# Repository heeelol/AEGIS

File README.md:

# AEGIS: AI-Enhanced Guidance and Inspection System

AEGIS is a computer vision and sensor-assisted system designed to reduce errors in manual kitting, the process by which a worker selects and packs a specified set of components into a single kit. The project was developed as the final year capstone for the CDE3301/IS305 module at the National University of Singapore (AY2025/26), in partnership with TE Connectivity and with hardware sponsorship from Advantech.

*The complete AEGIS workstation: overhead camera mount, load-cell bin platforms, operator dashboard, and the AI PC that runs the detection pipeline.*

## The Problem

In high-mix, low-volume manufacturing environments, kitting is performed manually because the variety of parts makes full automation impractical. This reliance on manual work introduces the risk of wrong parts, missing parts, and incorrect quantities. According to TE Connectivity, these errors account for an estimated USD 10,000 to USD 20,000 in losses per production line each year, largely because defects are only discovered downstream, where they are far more costly and difficult to trace back to their source.

## Our Approach

Rather than inspecting a kit after it has been packed, AEGIS observes the packing process as it happens. An overhead camera tracks the operator's hand movements to determine which bin is being accessed, while load cells positioned beneath each bin measure the change in weight for every pick. Together, these two independent signals allow the system to confirm, in real time, whether the correct item and the correct quantity have been taken. When a discrepancy is detected, the operator is alerted immediately through a dashboard interface, before the kit moves further down the line.

This dual-sensor design was a deliberate choice. Rather than requiring the system to visually identify each individual component, which is difficult given how frequently TE Connectivity's parts catalogue changes, AEGIS instead recognizes bins and cross-references their known contents with the weight removed. This keeps the system maintainable by production staff without requiring specialist machine learning expertise for every new part introduced.

## System Overview

The workstation is organized into three layers that work together as a closed loop:

- **Physical layer.** An aluminum-extrusion gantry holds the camera overhead and supports a modular arrangement of load-cell bin platforms and kitting bins.
- **Sensor layer.** A camera tracks the operator's hands, while load cells beneath each bin register mass changes as items are picked.
- **Software layer.** An edge processing engine, running locally on an Advantech MIC-733-AO industrial AI PC (built on an NVIDIA Jetson AGX Orin), combines the two sensor streams and checks them against the kit's bill of materials. Results are pushed to a dashboard on an Advantech FPM-215 touchscreen, giving the operator immediate, visual feedback.

Running all processing locally, rather than in the cloud, was a requirement from TE Connectivity to keep production data on-site and to avoid any dependence on network latency.

## Demonstration

A stitched video recording of the system in operation, combining the camera's point of view, the operator dashboard, and a third-person view of an operator performing a kitting task, can be viewed on YouTube: <https://youtu.be/AxHCu2dXehM>.

## Results

The system was evaluated through both developer-led testing and structured user testing with operators.

- Component identification was shown to be reliable across a range of lighting conditions and bin fill levels, and the backend fault-detection logic passed 134 unit tests covering 98 percent of the core decision-making code.
- In user testing with six operators, AEGIS was rated highly for communicating what to pack and how much to pack, and was generally preferred over a paper-based instruction sheet.
- The same testing also found that AEGIS introduced a consistent cycle-time increase of 35.2 percent across all operators, which did not meet the project's original performance target and is noted as the most significant area for further development.
- In a closing evaluation session, a TE Connectivity stakeholder rated the prototype's readiness for deployment at 80 percent, attributing most of the remaining gap to configuration workflow rather than to detection accuracy or hardware reliability.
- A cost analysis found that the base configuration of the system remains within budget expectations and pays for itself well inside a typical evaluation period.

Taken together, these findings support AEGIS as a proof of concept: the underlying idea, that errors can be caught at the moment they occur rather than after the fact, is validated, while its operating speed and ease of configuration remain the primary items to address before the system would be ready for a live production floor.

## Repository Structure

| Folder | Description |
| --- | --- |
| `final report/` | The final written report submitted for assessment, the demonstration video, supporting source material, and setup photography. |
| `aegis-v2/` | The current version of the bin-tracking and hand-tracking pipeline that powers the live system, along with its computer vision models and integration code. |
| `aegis-cv/` | Earlier computer vision model training and evaluation work. |
| `kitting-error-tracker/` | A standalone tool for tracking kitting errors during testing. |
| `esp32/` | Firmware and PCB design files for the load-cell electronics. |
| `Complete model/` | An earlier consolidated version of the detection and tracking pipeline. |

## Project Team

Developed by Lim Kai Ler Ethan, Aw Shuo Jie, Yap Jia Wei, and Yeo Chen Xian, under the supervision of Mr Chan Tong Leong and Mr Eugene Ee, as part of NUS's Engineering Design and Innovation Centre programme.

## Acknowledgements

We are grateful to TE Connectivity for the problem context and their continued involvement in testing and evaluating the prototype, and to Advantech for sponsoring the MIC-733-AO AI PC and FPM-215 HMI used throughout development. Full acknowledgements are included in the final report.

## Report

The complete final report, covering the problem context, design process, testing results, cost analysis, and conclusions in full, is available at [`final report/IS305 - Final Report - Submitted.pdf`](<final%20report/IS305%20-%20Final%20Report%20-%20Submitted.pdf>).

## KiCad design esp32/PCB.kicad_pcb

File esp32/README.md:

# AEGIS v2 — ESP32 Load-Cell Firmware

ESP32 firmware that reads an array of HX711 load-cell amplifiers and streams
per-bin weights to the host PC over USB serial. It is the device-side
counterpart to the host reader at
`aegis-v2/integration/src/sensing/loadcell.py`.

## What it does

Each load cell maps to one bin (`bin_{row}_{col}`). The ESP32 reads every cell,
applies per-bin calibration, and emits one line of JSON per cycle (~10 Hz):

```json
{"bins": {"bin_0_0": 123.4, "bin_0_1": 80.1, "bin_1_0": 0.0}}
```

Weights are in **grams**. The format, keys, and `115200` baud exactly match the
contract the host parser expects.

## Hardware

- 1× ESP32 dev board (any variant).
- 1× HX711 amplifier + load cell per bin (7 bins for the default `[4, 3]`
  layout).
- Each HX711 needs **VCC (3.3V), GND, DT (data), SCK (clock)**. DT/SCK go to the
  GPIO pins listed in `BINS[]`; VCC/GND share the ESP32's 3.3V and GND rails.

The example pins in `aegis_loadcells/aegis_loadcells.ino` are a starting point —
edit the `BINS[]` table to match your actual wiring and layout.

## Build & flash (Arduino IDE)

1. Install ESP32 board support: **File → Preferences →** add
   `https://raw.githubusercontent.com/espressif/arduino-esp32/gh-pages/package_esp32_index.json`
   to *Additional Board Manager URLs*, then install **esp32** in
   *Tools → Board → Boards Manager*.
2. Install the HX711 library: **Tools → Manage Libraries → "HX711" by Bogdan
   Necula** (bogde/HX711).
3. Open `aegis_loadcells/aegis_loadcells.ino`.
4. Select your board under **Tools → Board** and the serial port under
   **Tools → Port**, then click **Upload**.

(arduino-cli equivalent:)

```bash
arduino-cli core install esp32:esp32
arduino-cli lib install "HX711"
arduino-cli compile -b esp32:esp32:esp32 esp32/aegis_loadcells
arduino-cli upload  -b esp32:esp32:esp32 -p /dev/ttyUSB0 esp32/aegis_loadcells
```

## Calibration

Open the Arduino **Serial Monitor** at 115200 baud (newline line-ending). The
firmware streams JSON, and also accepts these one-line commands:

| Command       | Action                                                              |
|---------------|---------------------------------------------------------------------|
| `t`           | Tare (zero) every cell. Do this with all bins **empty**.            |
| `c <i> <g>`   | Calibrate cell index `<i>` using a known mass of `<g>` grams on it. |
| `r`           | Print the current pin/scale table.                                  |

To calibrate a cell:

1. Send `t` with empty bins.
2. Place a known weight (e.g. 500 g) on bin index `i`.
3. Send `c i 500`. The firmware prints the computed scale factor.
4. Paste that value into the `scale` column of `BINS[]` and re-flash so it
   persists across power cycles.

Command replies start with `#`, so the host parser ignores them harmlessly.

## Connect to the host pipeline

Enable load cells in `aegis-v2/integration/config/settings.yaml`:

```yaml
sensing:
  loadcells:
    enabled: true
    port: "/dev/ttyUSB0"   # ESP32 USB device (Windows: "COM3", macOS: "/dev/tty.usbserial-*")
    baudrate: 115200
    stale_after: 2.0
```

Find the port with `ls /dev/ttyUSB* /dev/ttyACM*` (Linux) or Device Manager
(Windows). The host reads weights on a background thread and the dashboard shows
live per-bin grams.

## Quick test without the pipeline

Any serial monitor at 115200 baud will show the JSON stream:

```bash
# Linux/macOS
screen /dev/ttyUSB0 115200      # Ctrl-A then K to quit
# or
python3 -m serial.tools.miniterm /dev/ttyUSB0 115200
```

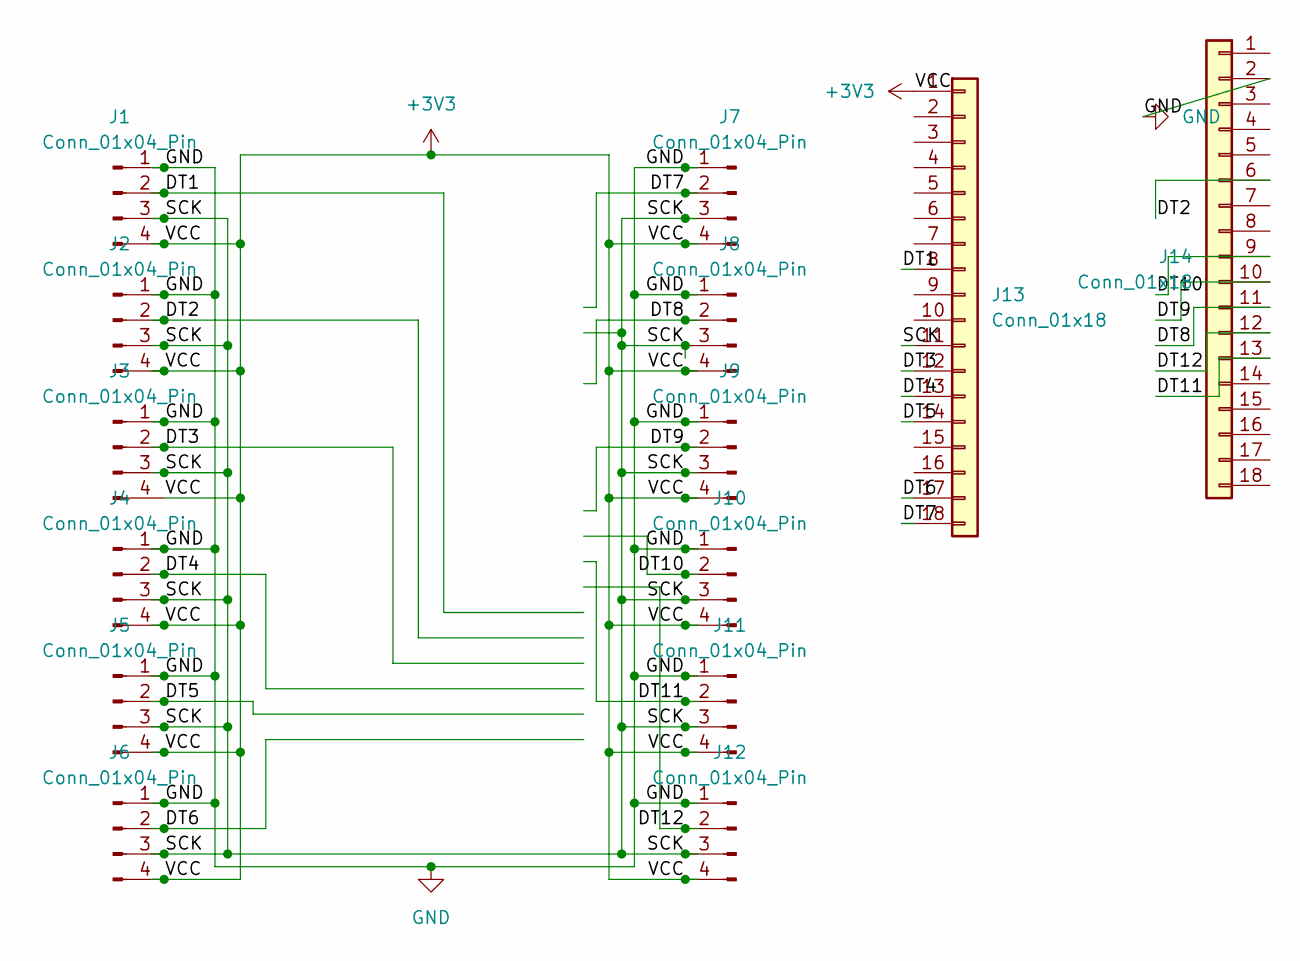
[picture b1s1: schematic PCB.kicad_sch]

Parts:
J1, J2, J3, J4, J5, J6, J7, J8, J9, J10, J11, J12: Conn_01x04_Pin; JST_XH_S4B-XH-A_1x04_P2.50mm_Horizontal
J13, J14: Conn_01x18; PinSocket_1x18_P2.54mm_Vertical

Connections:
+3V3: J1.4, J2.4, J3.4, J4.4, J5.4, J6.4, J7.4, J8.4, J9.4, J10.4, J11.4, J12.4, J13.1
/DT1: J1.2, J13.8
/DT2: J2.2, J14.6
/DT3: J3.2, J13.12
/DT4: J4.2, J13.13
/DT5: J5.2, J13.14
/DT6: J6.2, J13.17
/DT7: J7.2, J13.18
/DT8: J8.2, J14.11
/DT9: J9.2, J14.10
/DT10: J10.2, J14.9
/DT11: J11.2, J14.13
/DT12: J12.2, J14.12
/SCK: J1.3, J2.3, J3.3, J4.3, J5.3, J6.3, J7.3, J8.3, J9.3, J10.3, J11.3, J12.3, J13.11
GND: J1.1, J2.1, J3.1, J4.1, J5.1, J6.1, J7.1, J8.1, J9.1, J10.1, J11.1, J12.1, J14.2

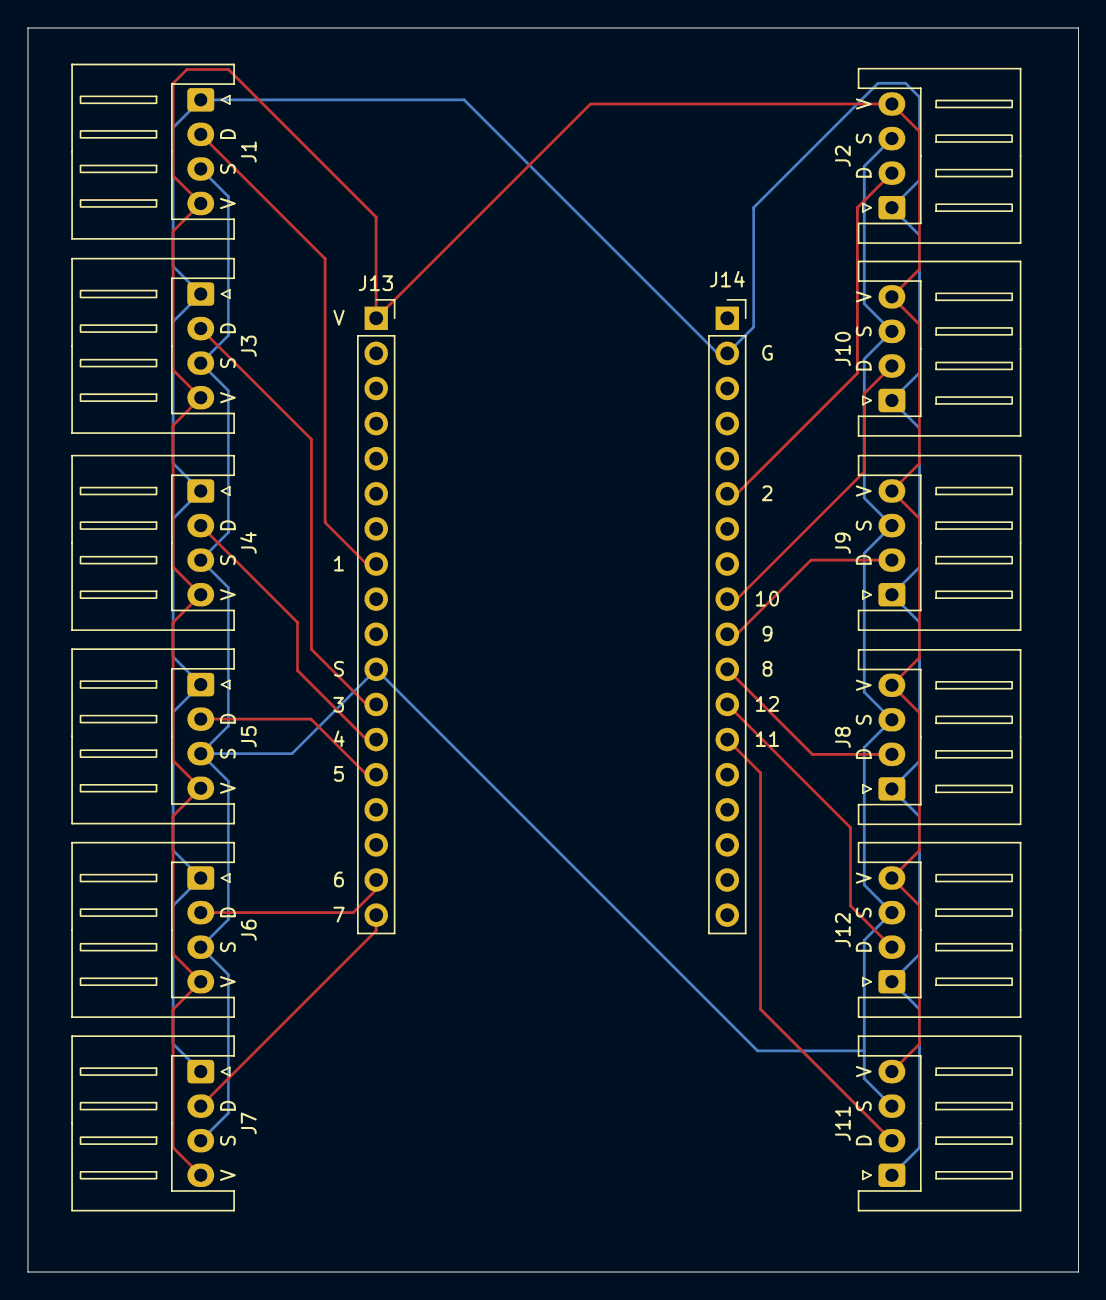
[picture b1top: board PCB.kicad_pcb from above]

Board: 2 copper layers, 76.0 x 90.0 mm, 14 parts (0 on the bottom side), 15 nets.

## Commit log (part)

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2026-06-10 stashed from main pipeline.py changes
2026-06-10 working loadcell to ui
2026-06-16 First Iteration of UI
    Current Problem Faced:
    - Two hands pick from 2 different bins of similar weight and look --> solve this by checking state at their respective bins when returning excess.
2026-06-16 loadcell added new te items
2026-06-16 Second iteration of UI
    - Removed redundant final kitting box UI
2026-06-17 multi loadcell sets working
2026-06-29 added magic numbers for gpio pins
2026-06-29 added calib numbers to most
2026-06-29 added calib numbers to loadcells 1-10 less 6 and 9
2026-06-30 updated inventory.yaml
